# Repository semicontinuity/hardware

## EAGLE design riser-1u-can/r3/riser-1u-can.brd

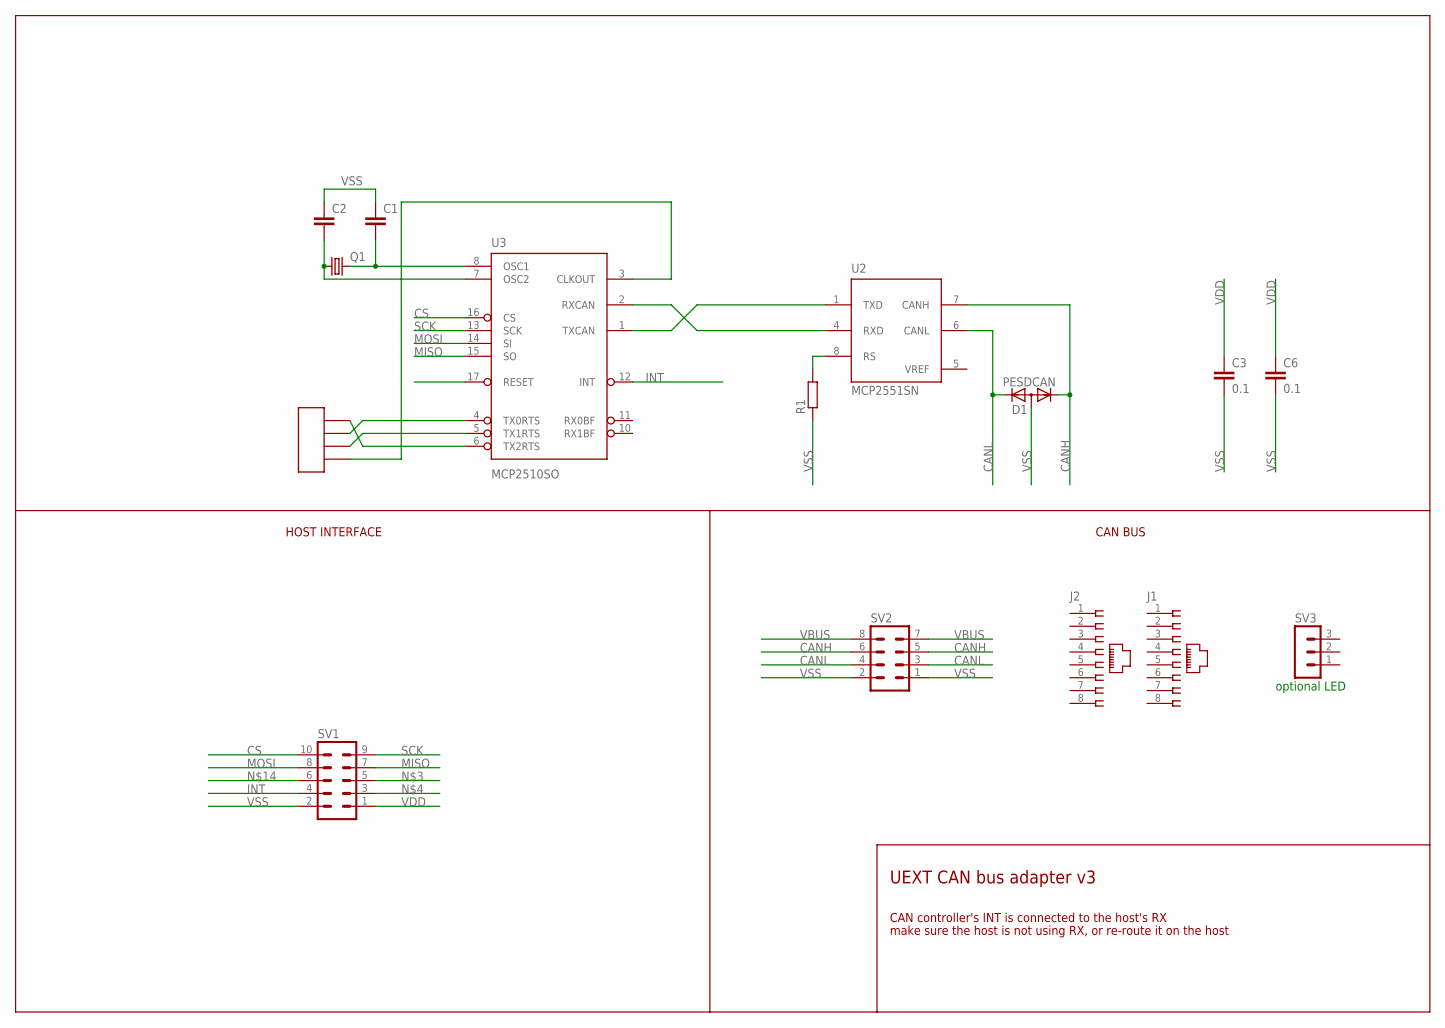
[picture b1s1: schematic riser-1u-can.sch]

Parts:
C1, C2: C-EUC0805; C0805
C3: 0.1; C0805
C6: 0.1; C1206
D1: PESDCAN; SOT23
J1, J2: 215877-4
Q1: CRYSTALHC49S; HC49/S
R1: R-EU_R0603; R0603
SV1: MA05-2
SV2: MA04-2
SV3: MA03-1
U2: MCP2551SN; SO-08
U3: MCP2510SO; SO-18W
U$2: PIN_HEADER_2X2

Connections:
CANH: D1.1 (K1), SV2.5, SV2.6, U2.7 (CANH)
CANL: D1.2 (K2), SV2.3, SV2.4, U2.6 (CANL)
CS: SV1.10, U3.16 (CS)
INT: SV1.4, U3.12 (INT)
MISO: SV1.7, U3.15 (SO)
MOSI: SV1.8, U3.14 (SI)
unnamed: C1.2, Q1.2, U3.8 (OSC1)
unnamed: C2.2, Q1.1, U3.7 (OSC2)
unnamed: U3.3 (CLKOUT), U$2.P$4
unnamed: U3.5 (TX1RTS), U$2.P$3
unnamed: U3.4 (TX0RTS), U$2.P$2
unnamed: U3.6 (TX2RTS), U$2.P$1
RESET_IN: U3.17 (RESET)
RS: R1.2, U2.8 (RS)
RXCAN: U2.4 (RXD), U3.2 (RXCAN)
SCK: SV1.9, U3.13 (SCK)
TXCAN: U2.1 (TXD), U3.1 (TXCAN)
VBUS: SV2.7, SV2.8
VDD: C3.1, C6.1, SV1.1, U2.3 (VDD), U3.18 (VDD)
VREF: U2.5 (VREF)
VSS: C1.1, C2.1, C3.2, C6.2, D1.3 (A), R1.1, SV1.2, SV2.1, SV2.2, U2.2 (VSS), U3.9 (VSS)

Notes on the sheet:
optional LED
HOST INTERFACE
CAN BUS
UEXT CAN bus adapter v3
CAN controller's INT is connected to the host's RX
make sure the host is not using RX, or re-route it on the host

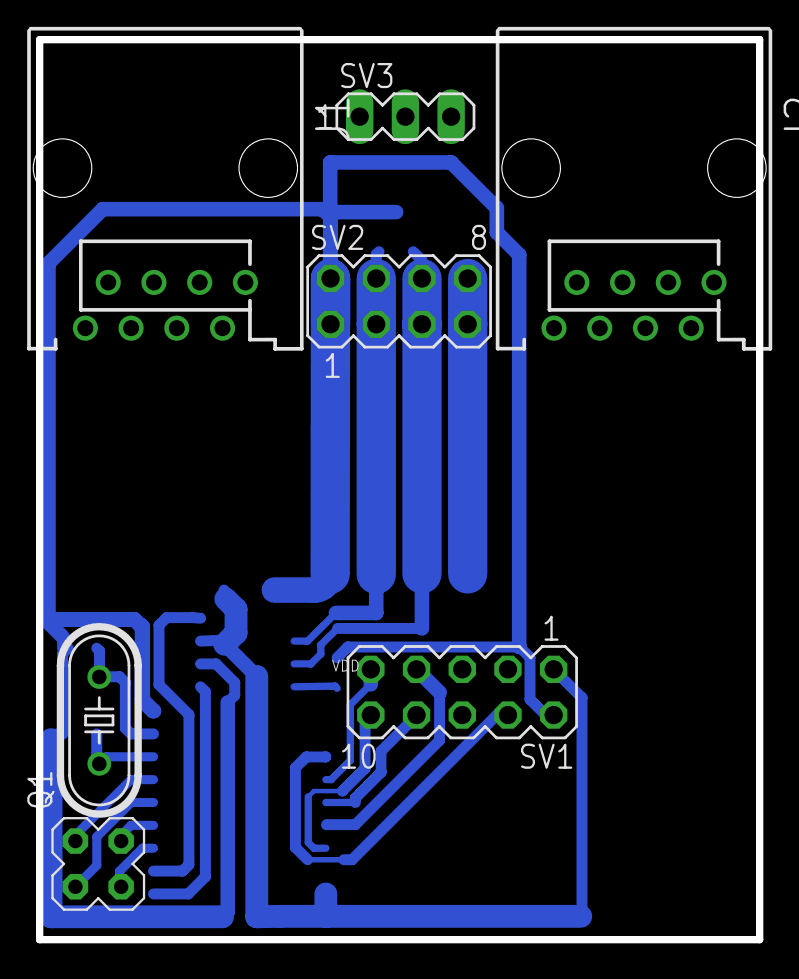
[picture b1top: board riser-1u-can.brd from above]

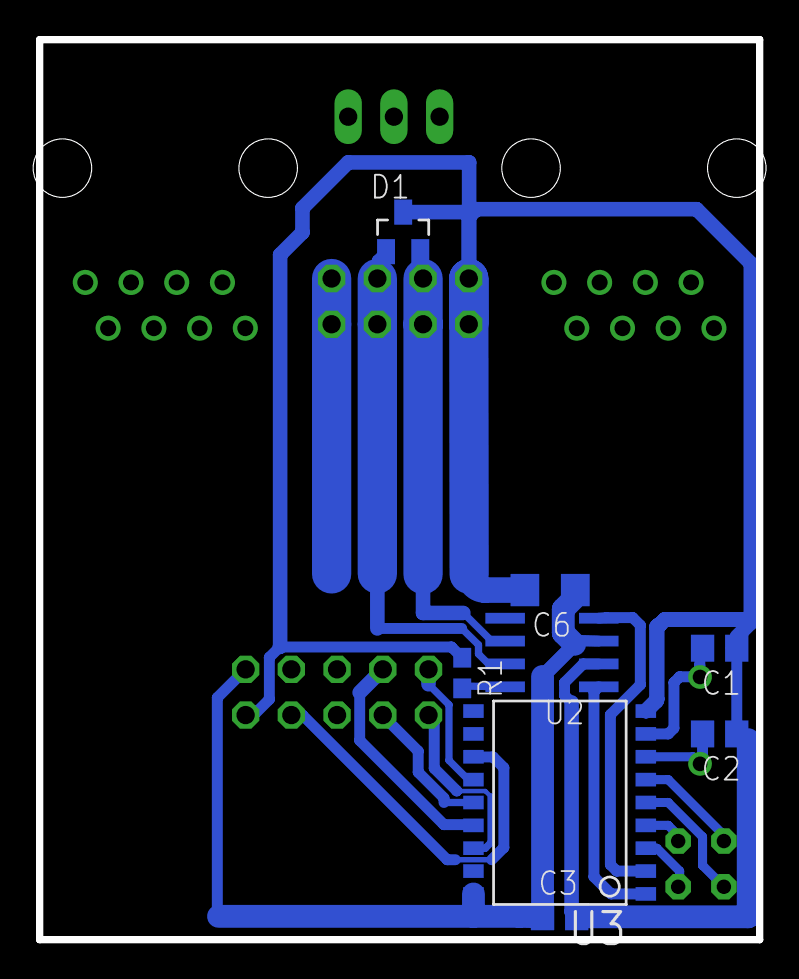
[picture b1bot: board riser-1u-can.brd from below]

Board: 2 copper layers, 40.0 x 50.0 mm, 15 parts (8 on the bottom side), 19 nets.

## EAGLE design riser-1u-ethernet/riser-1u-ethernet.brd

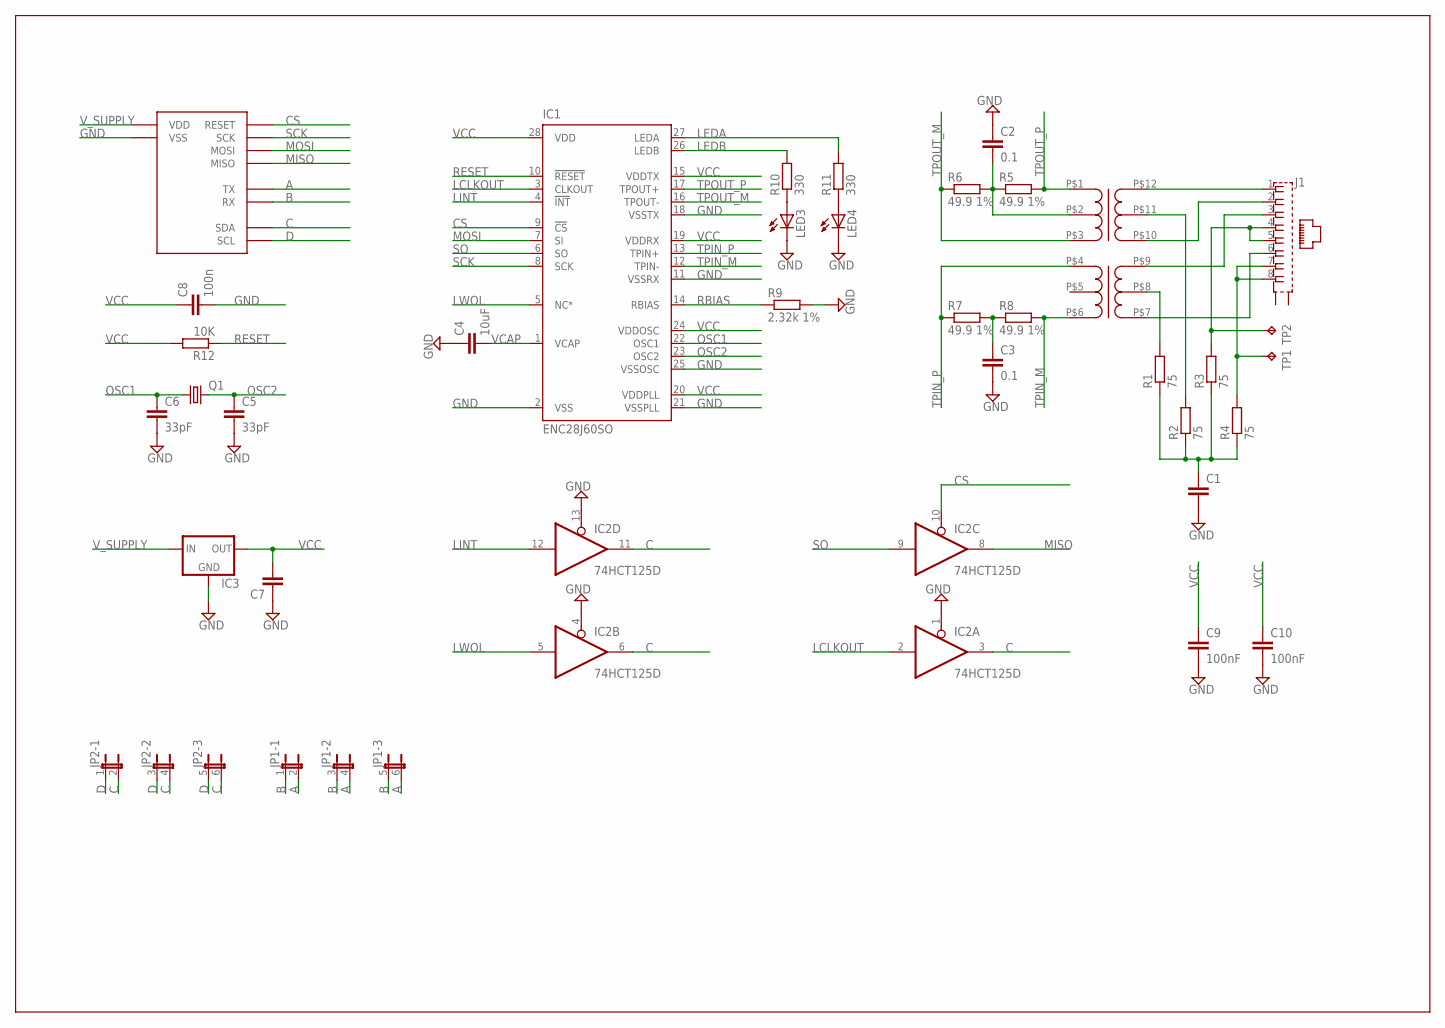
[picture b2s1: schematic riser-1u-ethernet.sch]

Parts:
C1: C-EU075-032X103; C075-032X103
C2, C3: 0.1; C0805
C4: 10uF; C1206
C5, C6: 33pF; C0805
C7: C-EUC1206; C1206
C8: 100n; C0805
C9, C10: 100nF; C0805
IC1: ENC28J60SO; SO28W
IC2: 74HCT125D; SO14
IC3: LM1117TO252; TO252
J1: 555153-1
JP1, JP2: JP3QE; JP3Q
LED3, LED4: LED3MM
Q1: CRYSTALHC49S; HC49/S
R1, R2, R3, R4: 75; R0805
R5, R6, R7, R8: 49.9 1%; R0805
R9: 2.32k 1%; R0805
R10, R11: 330; R0805
R12: 10K; R0805
TP1, TP2: TPPAD1-13; P1-13
U$1: UNI_BOARD_CONNECTOR_10; UNI_BOARD_CONN_10
U$2: ETHERNET_TRANSFORMER; DIL-16-TRANSFORMER

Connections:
A: JP1.2, JP1.4 (2), JP1.6 (2), U$1.C$7 (TX)
B: JP1.1, JP1.3 (1), JP1.5 (1), U$1.C$9 (RX)
C: IC2.3 (O), IC2.6 (O), IC2.11 (O), JP2.2, JP2.4 (2), JP2.6 (2), U$1.C$8 (SDA)
CS: IC1.9 (!CS), IC2.10 (OE), U$1.C$5 (RESET)
D: JP2.1, JP2.3 (1), JP2.5 (1), U$1.C$10 (SCL)
GND: C1.2, C2.1, C3.2, C4.1, C5.2, C6.2, C7.1, C8.2, C9.2, C10.2, IC1.2 (VSS), IC1.11 (VSSRX), IC1.18 (VSSTX), IC1.21 (VSSPLL), IC1.25 (VSSOSC), IC2.1 (OE), IC2.4 (OE), IC2.7 (GND), IC2.13 (OE), IC3.1 (GND), LED3.K (C), LED4.K (C), R9.2, U$1.C$6 (VSS)
LCLKOUT: IC1.3 (CLKOUT), IC2.2 (I)
LEDA: IC1.27 (LEDA), R11.2
LEDB: IC1.26 (LEDB), R10.2
LINT: IC1.4 (!INT), IC2.12 (I)
LWOL: IC1.5 (NC*), IC2.5 (I)
MISO: IC2.8 (O), U$1.C$1 (MISO)
MOSI: IC1.7 (SI), U$1.C$4 (MOSI)
unnamed: J1.1, U$2.P$12 (P16)
unnamed: J1.2, U$2.P$10 (P14)
unnamed: J1.3, U$2.P$9 (P11)
unnamed: J1.6, U$2.P$7 (P9)
unnamed: R1.2, U$2.P$8 (P10)
unnamed: R2.2, U$2.P$11 (P15)
unnamed: J1.4, J1.5, R3.2, TP2.TP
unnamed: J1.7, J1.8, R4.2, TP1.TP
unnamed: C1.1, R1.1, R2.1, R3.1, R4.1
unnamed: C2.2, R5.1, R6.2, U$2.P$2 (P2)
unnamed: C3.1, R7.2, R8.1
unnamed: LED3.A, R10.1
unnamed: LED4.A, R11.1
OSC1: C6.1, IC1.22 (OSC1), Q1.1
OSC2: C5.1, IC1.23 (OSC2), Q1.2
RBIAS: IC1.14 (RBIAS), R9.1
RESET: IC1.10 (!RESET), R12.1
SCK: IC1.8 (SCK), U$1.C$3 (SCK)
SO: IC1.6 (SO), IC2.9 (I)
TPIN_M: IC1.12 (TPIN-), R8.2, U$2.P$6 (P8)
TPIN_P: IC1.13 (TPIN+), R7.1, U$2.P$4 (P6)
TPOUT_M: IC1.16 (TPOUT-), R6.1, U$2.P$3 (P3)
TPOUT_P: IC1.17 (TPOUT+), R5.2, U$2.P$1 (P1)
VCAP: C4.2, IC1.1 (VCAP)
VCC: C7.2, C8.1, C9.1, C10.1, IC1.15 (VDDTX), IC1.19 (VDDRX), IC1.20 (VDDPLL), IC1.24 (VDDOSC), IC1.28 (VDD), IC2.14 (VCC), IC3.3 (OUT), R12.2
V_SUPPLY: IC3.2 (IN), U$1.C$2 (VDD)

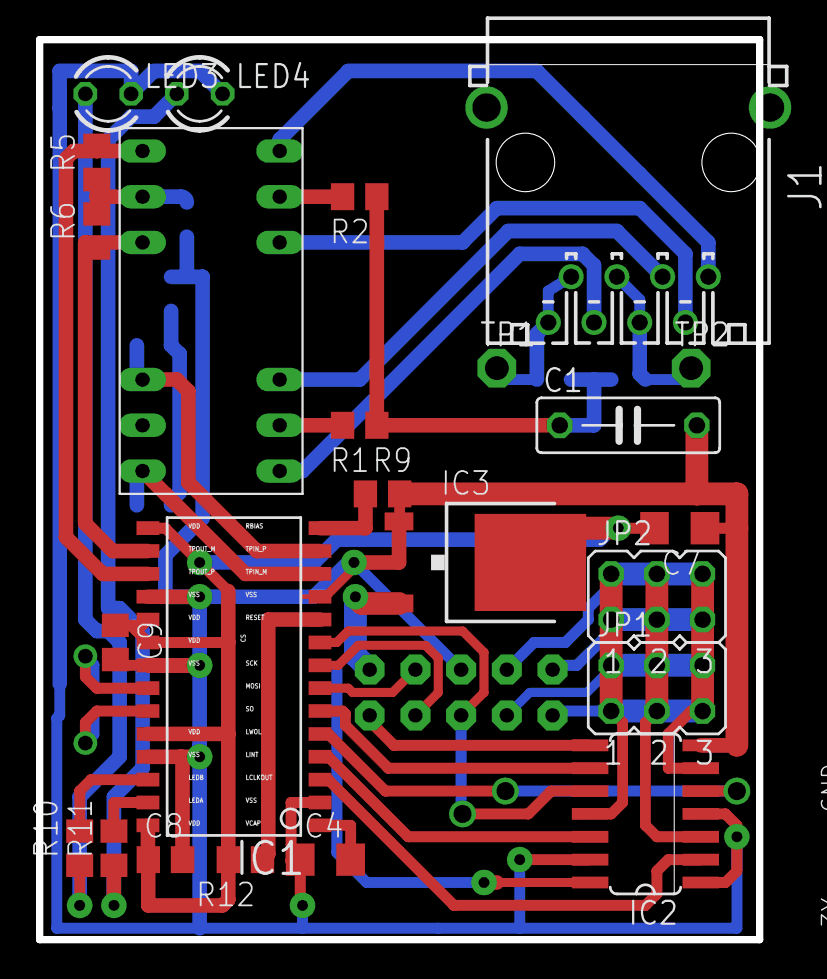
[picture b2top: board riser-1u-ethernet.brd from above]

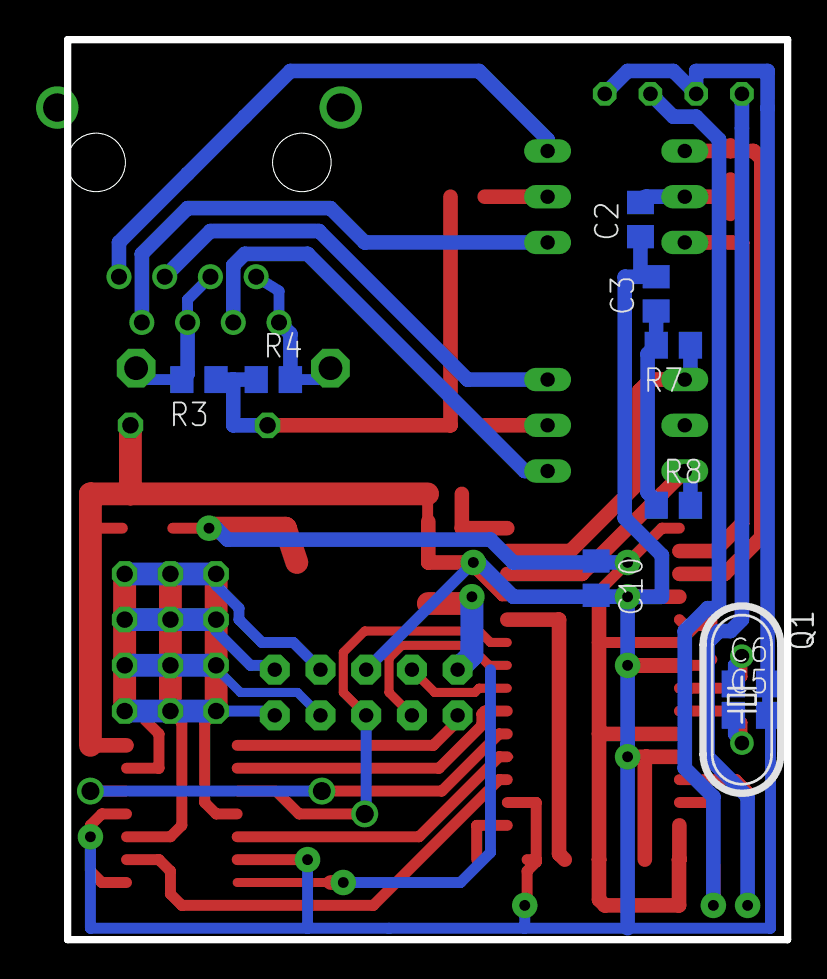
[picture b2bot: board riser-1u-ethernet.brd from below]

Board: 2 copper layers, 40.0 x 50.0 mm, 35 parts (10 on the bottom side), 39 nets.
